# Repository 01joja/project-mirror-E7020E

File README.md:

# Nuttali E7020E

We built a gaming mouse in 2 months. Project in Embedded System Design at LTU (E7020E).

Members:  
* Tommy Andersson - anetom-6  (Grade 5)
* Samuel Graden   - samgra-7  (Grade 5)
* Jonas Jacobsson - jonjac-6  (Grade 5)

Name *nuttali* is inspired from *Ochrotomys nuttalli* that is the *Latin* name for [golden mouse](https://en.wikipedia.org/wiki/Golden_mouse).

- Left and right buttons
- Scroll and "scroll button"
- 2 sidbutton
- Considering RGB.

Public found on: [Public](https://github.com/01joja/project-mirror-E7020E)

Course found on: [Course](https://gitlab.henriktjader.com/jonjac-6/nuttali-mirror-of-project)

## Version 0.0.2 is released!

- Side buttons, backwards and forwards now work
- RGB settings can now change mode from the DPI button
- Tested on Linux, Mac and Windows
- Created a customized report

## Version 0.0.1 is released!

The first release of our results in [E7020E](https://www.ltu.se/edu/course/E70/E7020E/E7020E-Design-av-inbyggda-system-1.67927?kursView=kursplan).

- PCB schematics and PCB board where every thing works.
- Rust code that supports basic mouse features:
  - Left, right and scroll click.  
  - Up and down scroll.
  - X and Y movement.
  - USB-communication.

### To be expected in later releases

- Fix error when connecting to some Windows devices.
- Support to change RGB for more values than 0 and 1.
- Fine tuning of sensor.
- A way to change settings by using the terminal.
- New design of scroll wheel.

[Presentation](presentation.md)

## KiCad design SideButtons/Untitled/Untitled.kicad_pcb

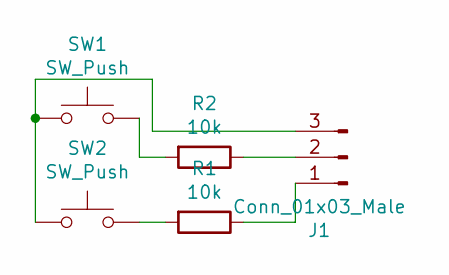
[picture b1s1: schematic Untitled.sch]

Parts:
J1: Conn_01x03_Male; PinHeader_1x03_P2.54mm_Vertical
R1, R2: 10k; R_0805_2012Metric_Pad1.20x1.40mm_HandSolder
SW1, SW2: SW_Push; D2F-5

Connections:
unnamed: J1.1, R1.1
unnamed: J1.2, R2.1
unnamed: J1.3, SW1.1, SW2.1
unnamed: R1.2, SW2.2
unnamed: R2.2, SW1.2

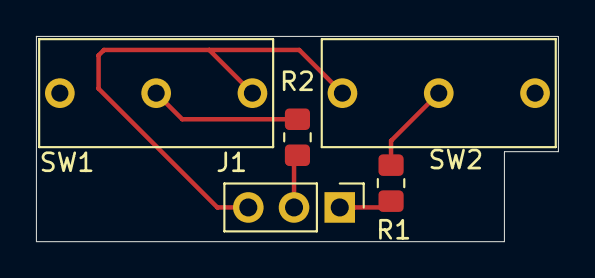
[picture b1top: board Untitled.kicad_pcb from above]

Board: 2 copper layers, 29.0 x 11.4 mm, 5 parts (0 on the bottom side), 5 nets.

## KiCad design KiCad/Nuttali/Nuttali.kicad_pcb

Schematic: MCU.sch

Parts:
C1, C6, C7, C8, C10, C11, C12, C13: 100nF; C_0805_2012Metric_Pad1.18x1.45mm_HandSolder
C2, C3: 22uF; C_0805_2012Metric_Pad1.18x1.45mm_HandSolder
C4, C5: 4.7uF; C_0805_2012Metric_Pad1.18x1.45mm_HandSolder
C9: 1uF; C_0805_2012Metric_Pad1.18x1.45mm_HandSolder
J1: SWD; PinHeader_1x06_P2.54mm_Vertical
J5: Conn_01x04_Male; PinSocket_1x04_P2.54mm_Vertical
R1: 10k; R_0805_2012Metric_Pad1.20x1.40mm_HandSolder
R16, R17, R18: 220; R_0805_2012Metric_Pad1.20x1.40mm_HandSolder
SW1: SW_DPST_x2; SW_SPST_B3U-1000P
SW2: RND 210-00662; PinHeader_1x03_P2.54mm_Vertical
TP7, TP8, TP9: TestPoint; TestPoint_Pad_1.0x1.0mm
U1: STM32F411RETx; LQFP-64_10x10mm_P0.5mm
Y1: 16Mhz; Crystal_SMD_0603-2Pin_6.0x3.5mm_HandSoldering

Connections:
+3V3: C5.1, C6.2, C7.2, C8.2, C9.2, C10.2, C11.1, C12.1, C13.1, J1.6, SW2.1 (A), U1.1 (VBAT), U1.13 (VDDA), U1.19 (VDD), U1.32 (VDD), U1.48 (VDD), U1.64 (VDD); also elsewhere on the board
BOOT0: SW2.2 (B), U1.60 (BOOT0)
B_LED: R18.2, U1.15 (PA1)
D+: TP8.1, U1.45 (PA12); also elsewhere on the board
D-: TP7.1, U1.44 (PA11); also elsewhere on the board
GND: C1.2, C2.2, C3.2, C4.1, C5.2, C6.1, C7.1, C8.1, C9.1, C10.1, C11.2, C12.2, C13.2, J1.4, J5.1, R1.1, SW1.1 (A), TP9.1, U1.12 (VSSA), U1.18 (VSS), U1.31 (VSS), U1.47 (VSS), U1.63 (VSS); also elsewhere on the board
G_LED: R17.2, U1.16 (PA2)
LeftB: U1.25 (PC5); also elsewhere on the board
MISO: U1.10 (PC2); also elsewhere on the board
MOSI: U1.11 (PC3); also elsewhere on the board
MOTION: U1.14 (PA0); also elsewhere on the board
NCS: U1.33 (PB12); also elsewhere on the board
NRESET: U1.8 (PC0); also elsewhere on the board
NRST: C1.1, J1.2, SW1.2 (B), U1.7 (NRST)
unnamed: C2.1, U1.5 (PH0), Y1.1
unnamed: C3.1, U1.6 (PH1), Y1.2
unnamed: C4.2, U1.30 (VCAP1)
unnamed: J5.2, R18.1
unnamed: J5.3, R17.1
unnamed: J5.4, R16.1
unnamed: R1.2, SW2.3 (C)
R_LED: R16.2, U1.17 (PA3)
RightB: U1.21 (PA5); also elsewhere on the board
SCK: U1.29 (PB10); also elsewhere on the board
SWCLK: J1.5, U1.49 (PA14)
SWDIO: J1.3, U1.46 (PA13)
SWO: J1.1, U1.55 (PB3)
SideBack: U1.36 (PB15); also elsewhere on the board
SideFront: U1.35 (PB14); also elsewhere on the board
Turbo: U1.20 (PA4); also elsewhere on the board
Turbo_LED: U1.26 (PB0); also elsewhere on the board
WheelA: U1.23 (PA7); also elsewhere on the board
WheelB: U1.24 (PC4); also elsewhere on the board
WheelButton: U1.22 (PA6); also elsewhere on the board

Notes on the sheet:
2*(Cload-Cstray)*2^(18-6)= 24pF = 22pF

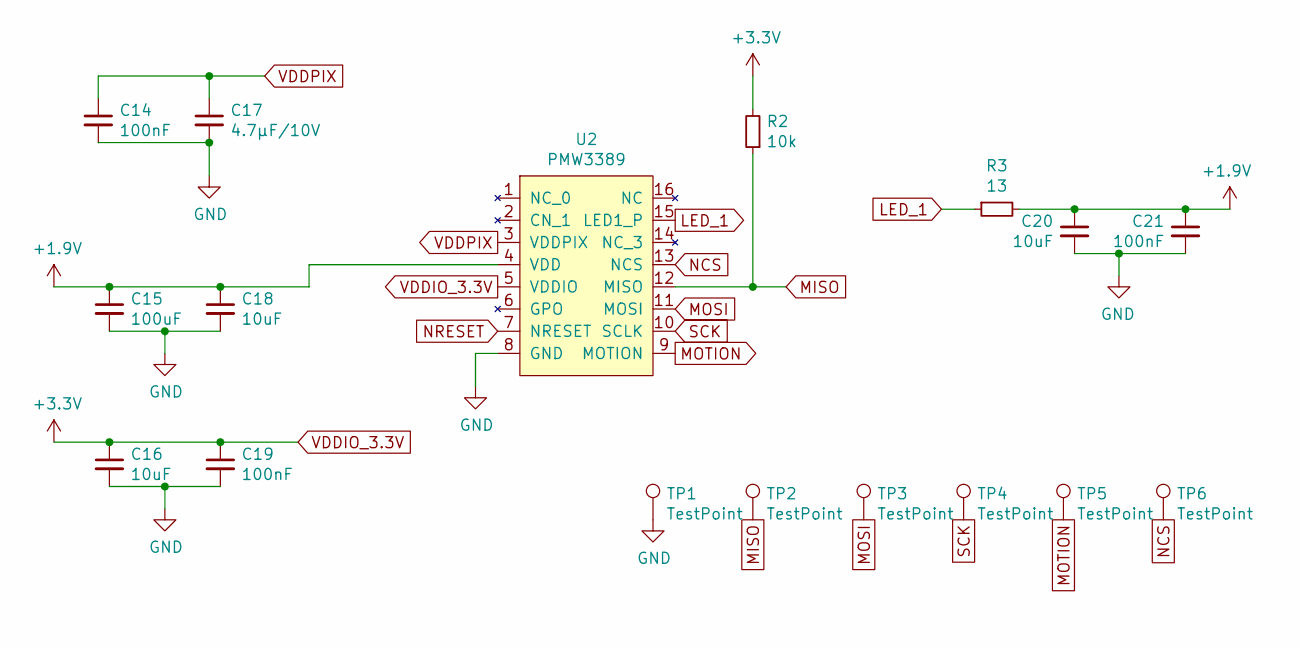
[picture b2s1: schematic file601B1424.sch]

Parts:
C14, C19, C21: 100nF; C_0805_2012Metric_Pad1.18x1.45mm_HandSolder
C15: 100uF; C_0805_2012Metric_Pad1.18x1.45mm_HandSolder
C16, C18, C20: 10uF; C_0805_2012Metric_Pad1.18x1.45mm_HandSolder
C17: 4.7μF/10V; C_0805_2012Metric_Pad1.18x1.45mm_HandSolder
R2: 10k; R_0805_2012Metric_Pad1.20x1.40mm_HandSolder
R3: 13; R_0805_2012Metric_Pad1.20x1.40mm_HandSolder
TP1, TP2, TP3, TP4, TP5, TP6: TestPoint; TestPoint_Pad_1.0x1.0mm
U2: PMW3389; PMW3389DM-T3QU

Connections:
+1V0: C15.1, C18.1, C20.1, C21.1, R3.2, U2.4 (VDD); also elsewhere on the board
+3V3: C16.1, C19.1, R2.2, U2.5 (VDDIO); also elsewhere on the board
GND: C14.2, C15.2, C16.2, C17.2, C18.2, C19.2, C20.2, C21.2, TP1.1, U2.8 (GND); also elsewhere on the board
LED_1: R3.1, U2.15 (LED1_P)
MISO: R2.1, TP2.1, U2.12 (MISO); also elsewhere on the board
MOSI: TP3.1, U2.11 (MOSI); also elsewhere on the board
MOTION: TP5.1, U2.9 (MOTION); also elsewhere on the board
NCS: TP6.1, U2.13 (NCS); also elsewhere on the board
NRESET: U2.7 (NRESET); also elsewhere on the board
SCK: TP4.1, U2.10 (SCLK); also elsewhere on the board
VDDPIX: C14.1, C17.1, U2.3 (VDDPIX)

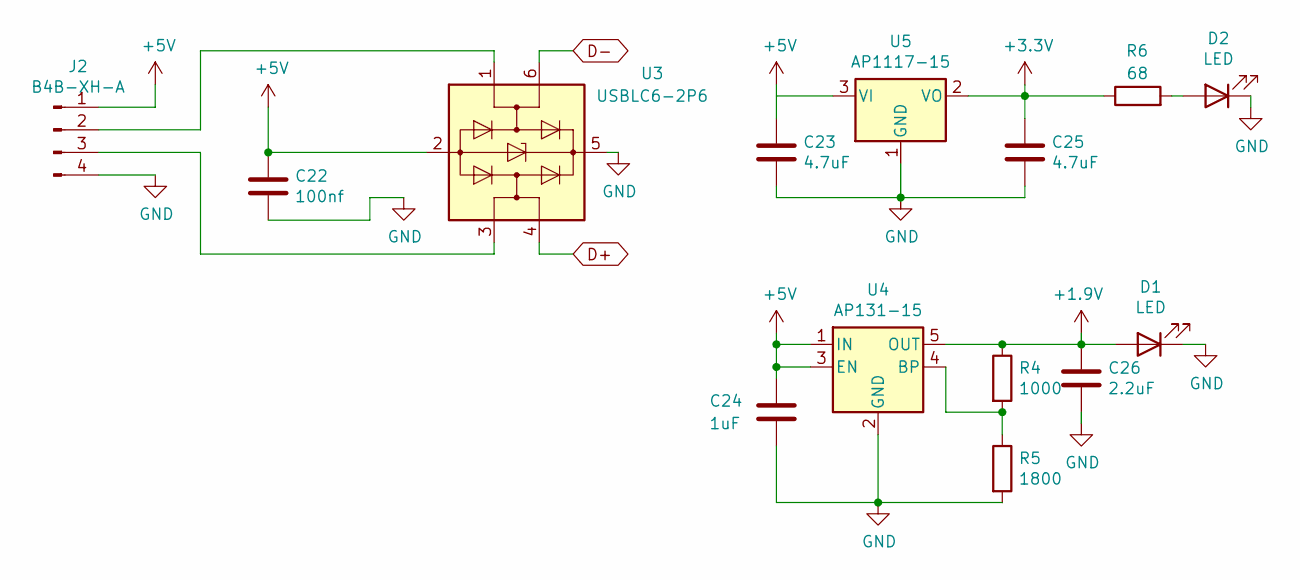
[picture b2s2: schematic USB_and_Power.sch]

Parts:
C22: 100nf; C_0805_2012Metric_Pad1.18x1.45mm_HandSolder
C23, C25: 4.7uF; C_0805_2012Metric_Pad1.18x1.45mm_HandSolder
C24: 1uF; C_0805_2012Metric_Pad1.18x1.45mm_HandSolder
C26: 2.2uF; C_0805_2012Metric_Pad1.18x1.45mm_HandSolder
D1, D2: LED
J2: B4B-XH-A; PinHeader_1x04_P2.54mm_Vertical
R4: 1000; R_0805_2012Metric_Pad1.20x1.40mm_HandSolder
R5: 1800; R_0805_2012Metric_Pad1.20x1.40mm_HandSolder
R6: 68; R_0805_2012Metric_Pad1.20x1.40mm_HandSolder
U3: USBLC6-2P6; SOT-666_ESD
U4: AP131-15; SOT-23-5
U5: AP1117-15; SOT-23

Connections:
+1V0: C26.1, D1.2 (A), R4.1, U4.5 (OUT); also elsewhere on the board
+3V3: C25.1, R6.1, U5.2 (VO); also elsewhere on the board
+5V: C22.1, C23.1, C24.1, J2.1, U3.2 (GND), U4.1 (IN), U4.3 (EN), U5.3 (VI)
D+: U3.4 (I/O2); also elsewhere on the board
D-: U3.6 (I/O1); also elsewhere on the board
GND: C22.2, C23.2, C24.2, C25.2, C26.2, D1.1 (K), D2.1 (K), J2.4, R5.2, U3.5 (VBUS), U4.2 (GND), U5.1 (GND); also elsewhere on the board
unnamed: D2.2 (A), R6.2
unnamed: J2.2, U3.1 (I/O1)
unnamed: J2.3, U3.3 (I/O2)
unnamed: R4.2, R5.1, U4.4 (BP)

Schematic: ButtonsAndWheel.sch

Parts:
C27, C28, C29, C30: C; C_0805_2012Metric_Pad1.18x1.45mm_HandSolder
J3: Conn_01x03_Male; PinSocket_1x03_P2.54mm_Vertical
J4: Conn_01x02_Male; PinSocket_1x02_P2.54mm_Vertical
R7, R8, R11, R12, R13, R15: 10k; R_0805_2012Metric_Pad1.20x1.40mm_HandSolder
SW8: Rotary_Encoder; Encoder
TP10, TP11, TP12, TP13, TP14, TP15: TestPoint; TestPoint_Pad_1.0x1.0mm
U6, U7, U9: Button; D2F-5
U8: Scroll_button

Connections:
+3V3: J3.1, R7.2, R8.1, R11.1, R12.2, R13.1, R15.2; also elsewhere on the board
GND: C27.2, C28.2, C29.2, C30.1, J4.1, SW8.C, U6.2 (NO), U7.2 (NO); also elsewhere on the board
LeftB: C28.1, TP10.1, U6.1 (Com); also elsewhere on the board
unnamed: R7.1, U7.3 (NC)
unnamed: R8.2, U6.3 (NC)
unnamed: R13.2, U8.3
unnamed: R15.1, U9.1 (Com)
RightB: C27.1, TP11.1, U7.1 (Com); also elsewhere on the board
SideBack: J3.2; also elsewhere on the board
SideFront: J3.3; also elsewhere on the board
Turbo: TP15.1, U9.2 (NO); also elsewhere on the board
Turbo_LED: J4.2; also elsewhere on the board
WheelA: C29.1, R11.2, SW8.A, TP13.1; also elsewhere on the board
WheelB: C30.2, R12.1, SW8.B, TP14.1; also elsewhere on the board
WheelButton: TP12.1, U8.2; also elsewhere on the board

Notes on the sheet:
Left and right click
Side buttons
Scroll wheel
Top buttons
To connect the side buttons since they will be on different pcb

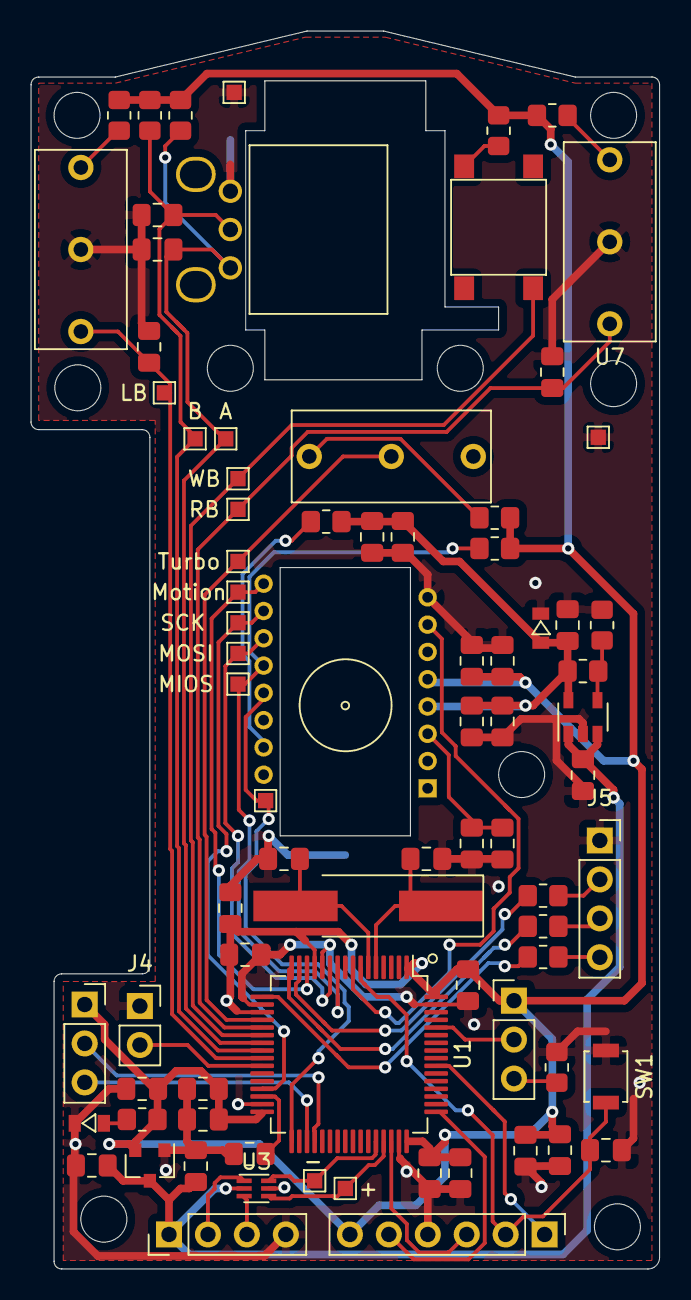
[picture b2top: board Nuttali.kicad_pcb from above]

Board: 2 copper layers, 41.0 x 80.8 mm, 80 parts (0 on the bottom side), 46 nets.

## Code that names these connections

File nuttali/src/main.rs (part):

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    //dwt::Dwt,
    gpio::Speed,
    //Look at resources to see what pin belongs to what.
    gpio::{gpioa::{PA1, PA2, PA3, PA4, PA5, PA6, PA7},
        gpiob::{PB10, PB12, PB14,PB15},
        gpioc::{PC2, PC3, PC4, PC5},
        Alternate, Output, PushPull, Input, PullDown,// PullUp, 
    },
    //rcc::Clocks,
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    Spi<
        stm32f4xx_hal::stm32::SPI2,
        (
            PB10<Alternate<stm32f4xx_hal::gpio::AF5>>,
            PC2<Alternate<stm32f4xx_hal::gpio::AF5>>,
            PC3<Alternate<stm32f4xx_hal::gpio::AF5>>,
        ),
    >,
    PB12<Output<PushPull>>,
>;

//Report for USB.
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    struct Resources {
        // late resources
        // Leds
        led_blue: PA1<Output<PushPull>>,
        led_red:  PA3<Output<PushPull>>,
        led_green: PA2<Output<PushPull>>,

        // Buttons
        dpi_button: PA4<Input<PullDown>>,
        right_button: PA5<Input<PullDown>>,
        scroll_button: PA6<Input<PullDown>>,
        backward_button: PB15<Input<PullDown>>,
        forward_button: PB14<Input<PullDown>>,
        left_button: PC5<Input<PullDown>>,

        // Scroll
        scroll_B: PC4<Input<PullDown>>,
        scroll_A: PA7<Input<PullDown>>,

        // USB
        hid: HIDClass<'static, UsbBusType>,
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        ctx.core.DWT.enable_cycle_counter();

        // Leds
        let led_red = gpioa.pa3.into_push_pull_output();
        let led_green = gpioa.pa2.into_push_pull_output();
        let led_blue = gpioa.pa1.into_push_pull_output();
        
        // Buttons
        let left_button = gpioc.pc5.into_pull_down_input();
        let right_button = gpioa.pa5.into_pull_down_input();
        let scroll_button = gpioa.pa6.into_pull_down_input();
        let backward_button = gpiob.pb15.into_pull_down_input();
        let forward_button = gpiob.pb14.into_pull_down_input();
        let dpi_button = gpioa.pa4.into_pull_down_input();

        //Scroll
        let scroll_A = gpioa.pa7.into_pull_down_input();
        let scroll_B = gpioc.pc4.into_pull_down_input();

        // Sensor Init
        // ||||||||||
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        rprintln!("hclk {}", _clocks.hclk().0);

        // Configure SPI
        let sck = gpiob.pb10.into_alternate_af5();
        let miso = gpioc.pc2.into_alternate_af5();
        let mosi = gpioc.pc3.into_alternate_af5();
        let cs = gpiob.pb12.into_push_pull_output().set_speed(Speed::High);

        let spi = Spi::spi2(
            ctx.device.SPI2,
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
        // Pull the D+ pin down to send a RESET condition to the USB bus.
        // Dose not work yet.
        //let mut usb_dp = gpioa.pa12.into_alternate_af10();
        //usb_dp= false;
        //delay(_clocks.sysclk().0 / 100);

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            usb_global: ctx.device.OTG_FS_GLOBAL,
            usb_device: ctx.device.OTG_FS_DEVICE,
            usb_pwrclk: ctx.device.OTG_FS_PWRCLK,
            pin_dm: gpioa.pa11.into_alternate_af10(),
            pin_dp: gpioa.pa12.into_alternate_af10(),
        };

        USB_BUS.replace(UsbBus::new(usb, EP_MEMORY));
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
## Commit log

2021-01-26 Features
2021-02-02 Add new file
2021-02-03 Added a .gitignore for Rust and KiCad.
2021-02-03 Kicad
2021-02-03 created pmw
2021-02-04 Set up rust in the project
2021-02-04 Small changes on PMW
2021-02-04 Fixed MCU
2021-02-04 Fixed power and USB
2021-02-05 documents
2021-02-05 Added all lectures to this branch
2021-02-05 found a example of a mouse
2021-02-05 Added buttons
2021-02-05 Added scroolWheel and rgb
2021-02-05 Test
2021-02-10 some footprints fixed
2021-02-10 Footprint
2021-02-10 all footprints fixed
2021-02-10 First draft of the pcb
2021-02-11 Working on the new pcb
2021-02-12 Soon done with the pcb
2021-02-12 created foot print for encoder
2021-02-12 pushing a few things
2021-02-12 SideButtonXtreme3000
2021-02-13 extended the pcb board with 2 mm to right
2021-02-13 footprint for omron switches done
2021-02-13 Fixed almost all footprints and nearly the layout of the pcb
2021-02-13 Missed saving things
2021-02-14 Finnished the pcb
2021-02-14 Finnished design.
2021-02-14 Changed routes on the scroll wheel button
2021-02-14 Chnages footprint of esd
2021-02-14 SideButton Nya Knappar
2021-02-14 Last push befor ordering
2021-02-14 PCB done
2021-03-15 added pers things to project
2021-03-19 added some things
2021-03-22 renamed some files
2021-03-22 added per exampels
2021-03-22 All buttons are registering but scroll forward and backwards needs tuning. No anti button bouncing implemented.
2021-03-22 changed scroll
2021-03-22 Fixed scroll
2021-03-22 added a counter and some text to the file
2021-03-23 Left and right button working. Started integrating the sensor code.
2021-03-23 Updated with the sensor, it's working but have some issues. Might need to change protocol.
2021-03-23 changed stuff
2021-03-23 changed things in usb-mouse
2021-03-24 got the sensor, scroll and left button to work on windows.
2021-03-24 Have now a working mouse
2021-03-24 Fixed scroll.
2021-03-24 lowerd the speed of the sensor
2021-03-24 removed warnings
2021-03-24 rebased on master
2021-03-24 Added usb_mouse as a new file to avoid merge conflicts and loss of data. DPI button and rgb working.
2021-03-25 changed readme
2021-03-25 changed in presentation
2021-03-25 added presentations files
2021-03-25 Mötesantäckningar
2021-03-25 Gaming mouse
2021-03-25 Finnished with hardwhare designpart
2021-03-25 Added Requirements specification/features and Hardware
2021-03-25 Update with testing and validation
2021-03-25 mouse under the hood
2021-03-25 All the different iterations
2021-03-25 Tommy mouse
2021-03-25 pcb version 2
2021-03-25 verion 3 pcb
2021-03-25 pcb support
2021-03-25 worksheet
2021-03-25 buttons
2021-03-26 I am not done but I am working on it
2021-03-26 Updated with fancy RGB.
2021-03-26 Forward and backward finnally work
2021-03-26 Updated main
2021-03-26 Version 0.0.2 released.
2021-03-26 Merged/Added rgb to main.rs
2021-03-26 removed all errors
2021-03-26 Added known buggs to readme.
2021-03-26 added two dots on the presentation
2021-03-26 changed small problems
2021-03-26 small changes to presentation
2021-03-26 Final changes
